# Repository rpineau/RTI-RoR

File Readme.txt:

This plugin allows you to control a dome rotation and shutter with the NexDome Dome Rotation Kit (http://www.nexdome.com/#!product-page/gba22/79b04628-9935-5ea7-9c5b-6936abac9900 ) from NexDome (shutter control should be available soon too).
This was developed and tested using a "desk" dome (see picture on my website).

The NexDome Rotation Kit firmware can be found on Gerry Rozema's GitHub : https://github.com/grozzie2/NexDome

Pre-compiled versions for OS X, Windows, Unbuntu X86_64 and Rapsberry Pi Pixel can be found there :
http://www.rti-zone.org/macosx_x2dome_plugins.php

Rodolphe

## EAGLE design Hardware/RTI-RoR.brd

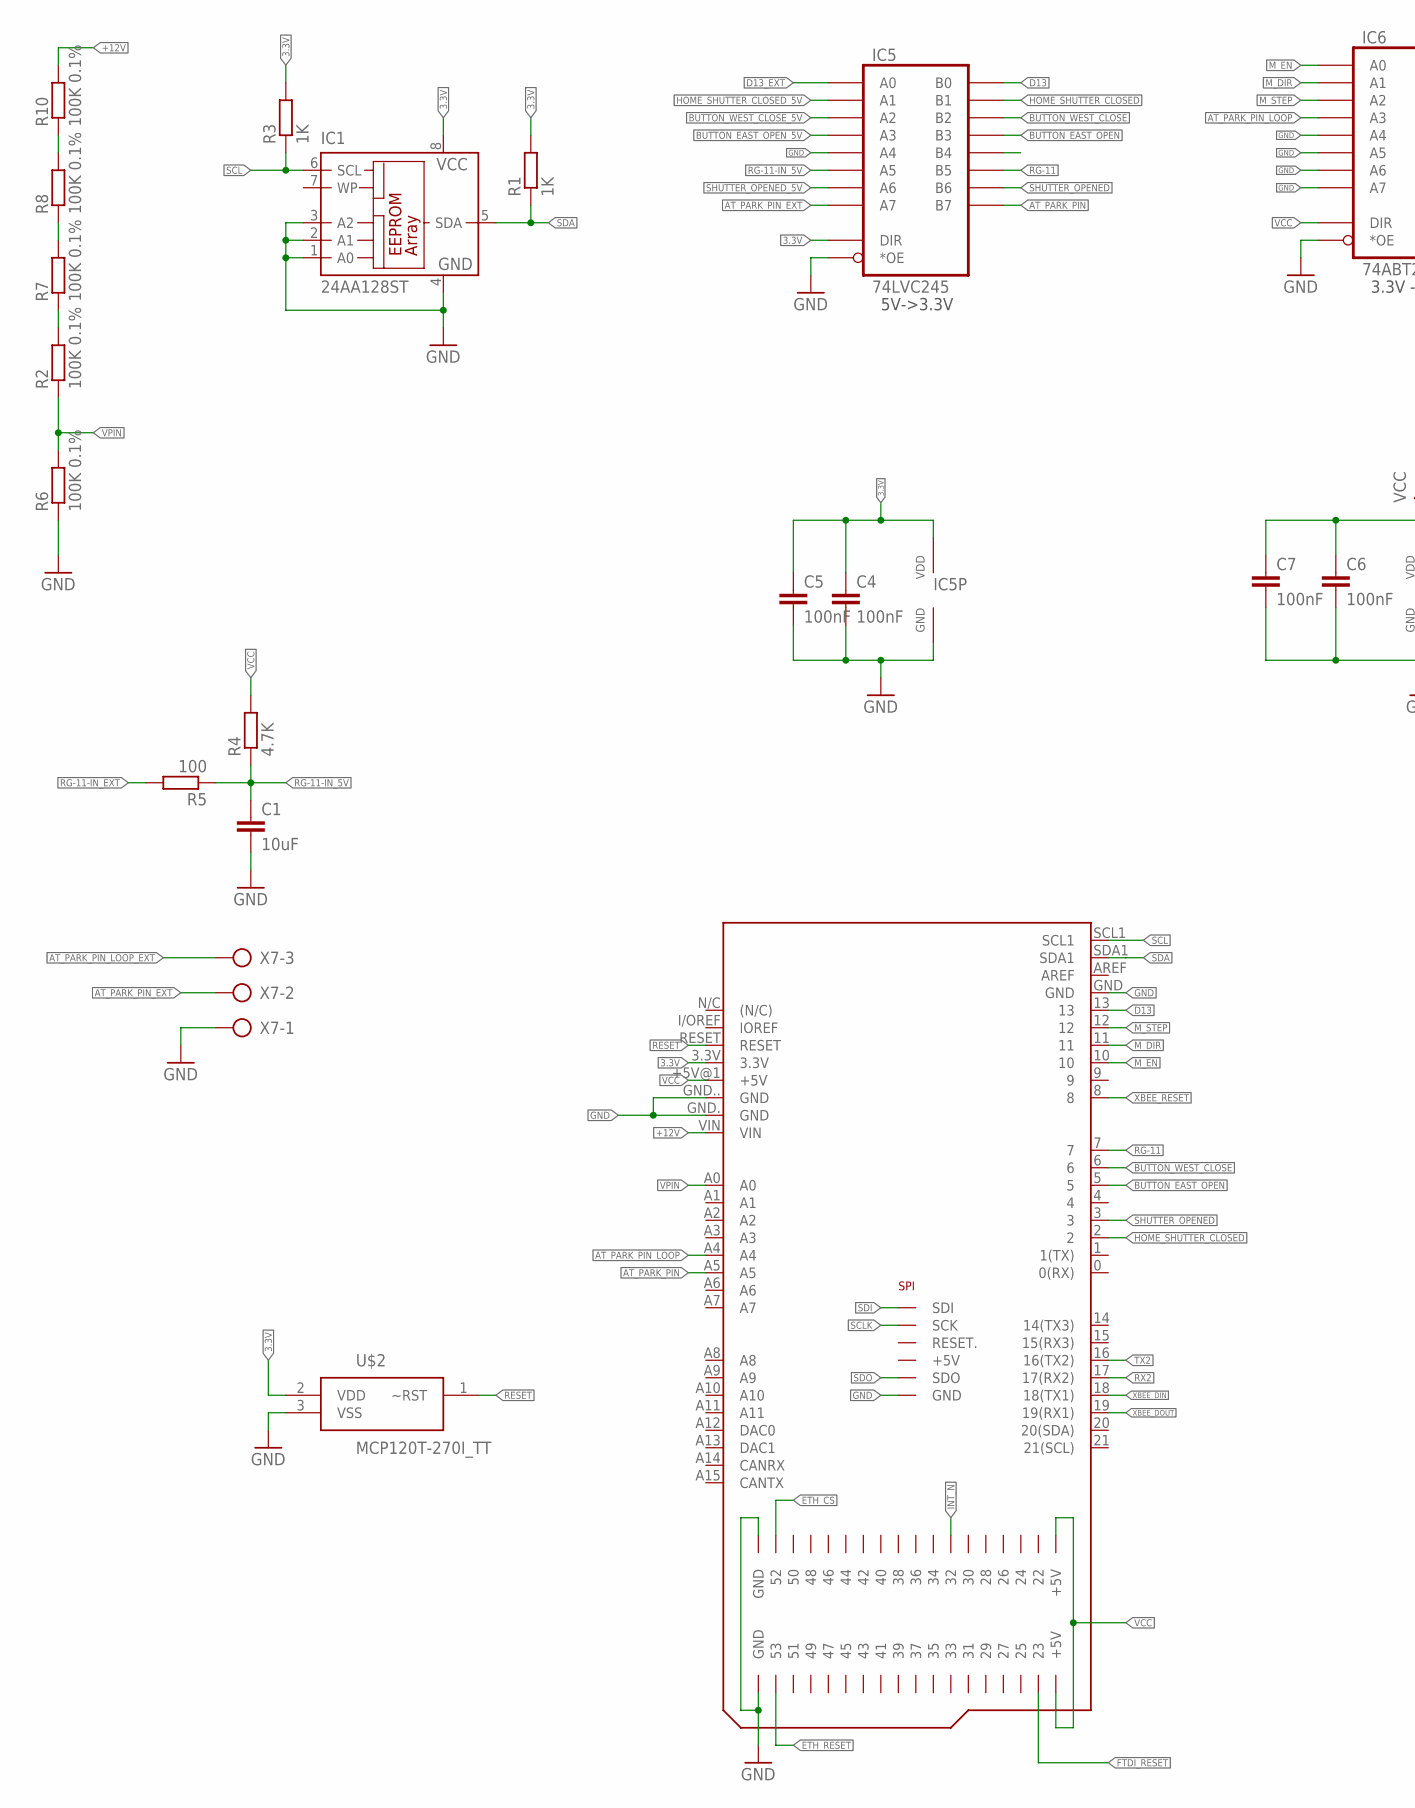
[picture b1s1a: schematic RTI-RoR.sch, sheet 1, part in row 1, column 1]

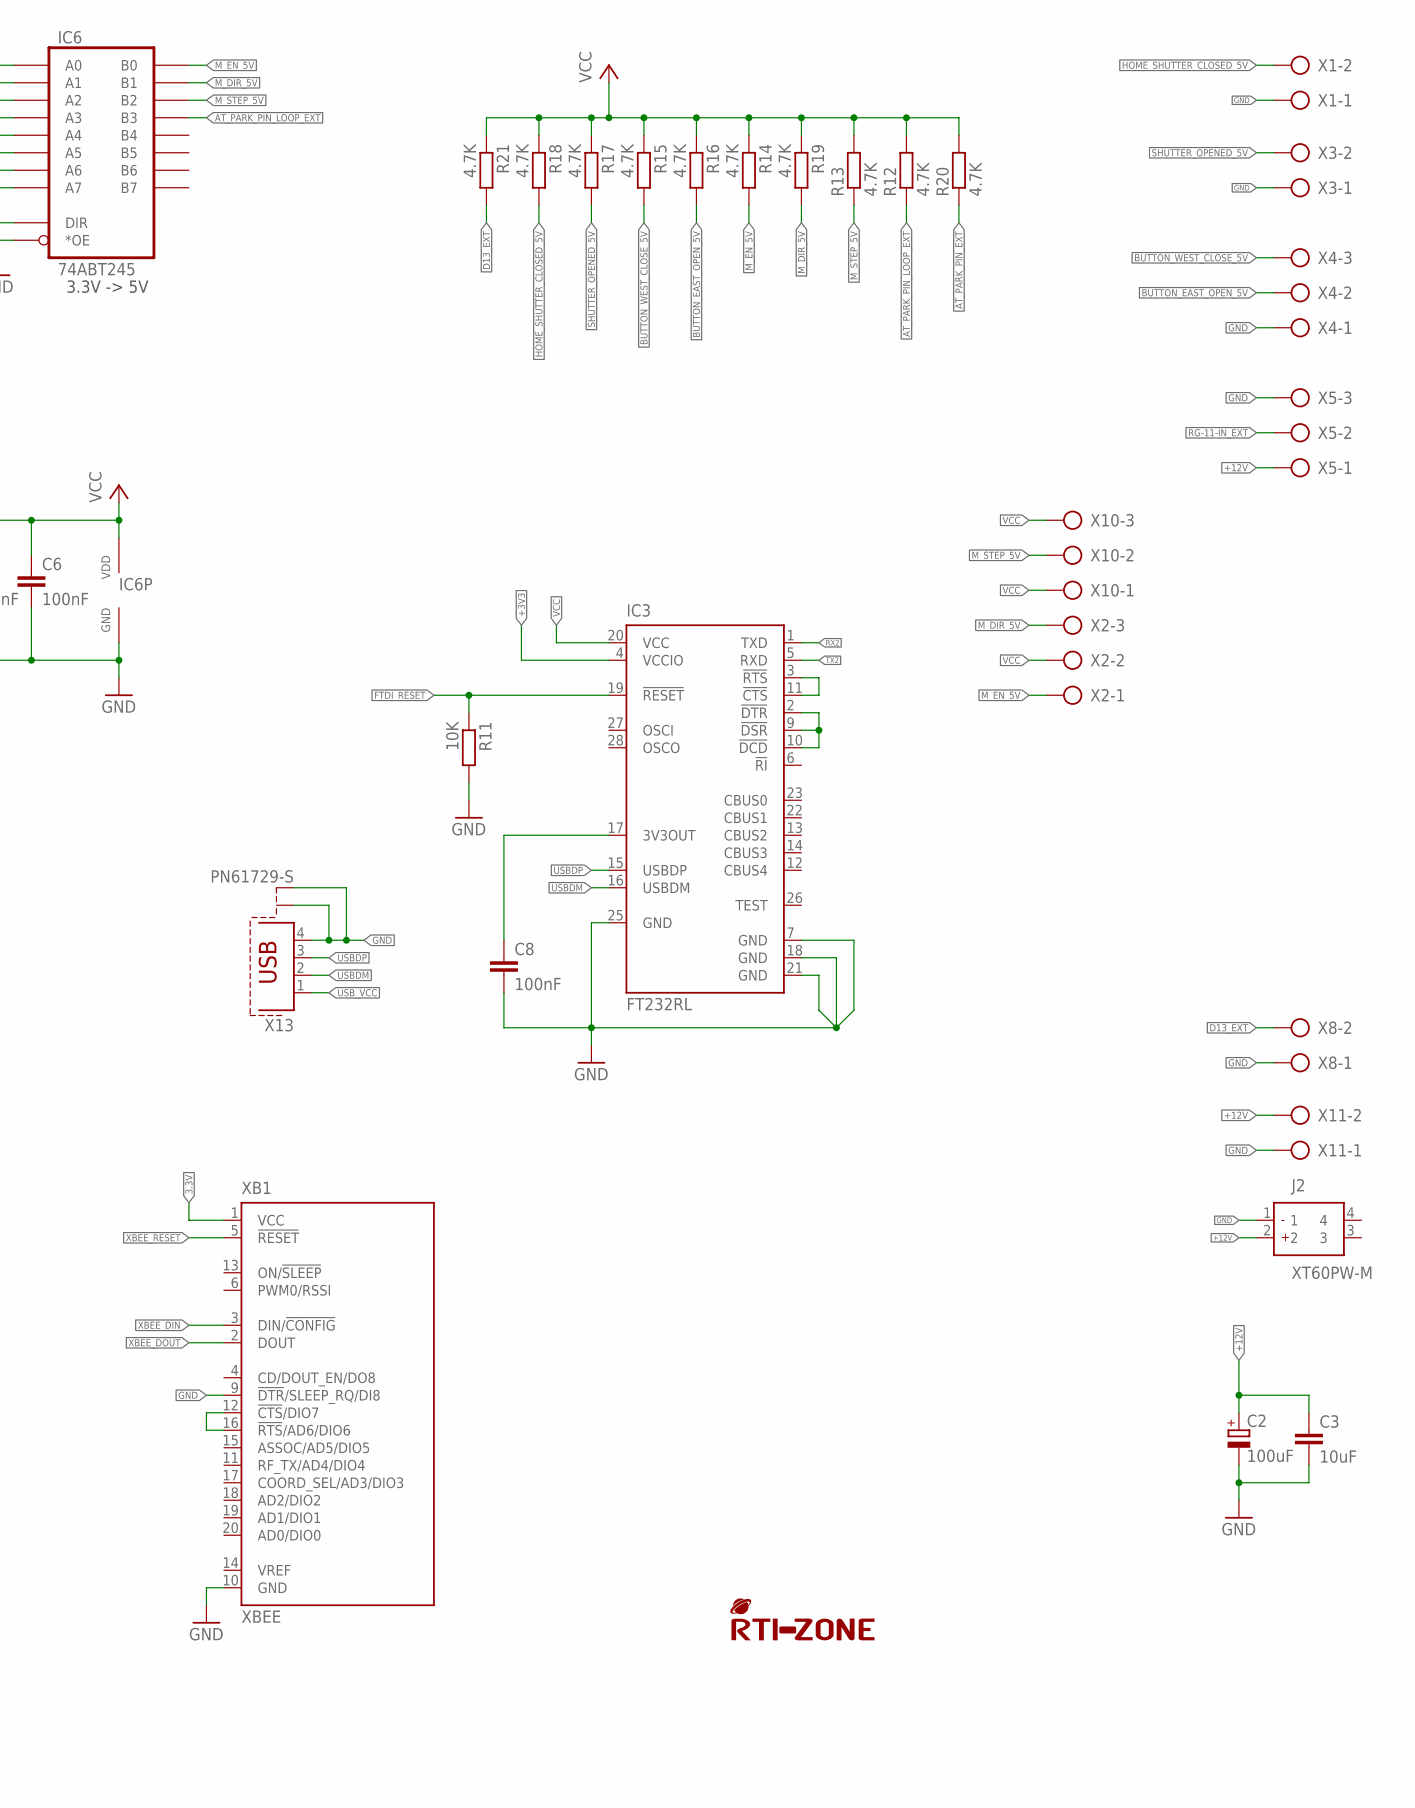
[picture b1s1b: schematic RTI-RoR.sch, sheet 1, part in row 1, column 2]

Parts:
C1, C3: 10uF; C0805; MPN CC0805KKX5R8BB106
C2: 100uF; UD-10X10_NICHICON; MPN MAL215099804E3
C4, C5, C6, C7, C8: 100nF; C0805; MPN 0805YD104KAT2A
IC1: 24AA128ST; TSSOP8
IC3: FT232RL; SSOP28; MPN FT232RL-REEL
IC5: 74LVC245; TSSOP20; MPN 74LVC245APW,112
IC6: 74ABT245; TSSOP20; MPN 74ABT245PW,112
J2: XT60PW-M; XT60PWM
R1, R3: 1K; R0805; MPN RT0805FRE071KL
R2, R6, R7, R8, R10: 100K 0.1%; R0805; MPN AT0805BRD07100KL
R4, R12, R13, R14, R15, R16, R17, R18, R19, R20, R21: 4.7K; R0805; MPN RT0805FRE074K7L
R5: 100; R0805; MPN RT0805FRD07100RL
R11: 10K; R0805; MPN RT0805FRE0710KL
U$1: ARDUINO_DUE_SHIELD_FULL
U$2: MCP120T-270I_TT; SOT95P237X112-3N; MPN MCP120T-270I/TT
U$4: RTI-LOGO_BIG; LOGO_BIG
X1, X3, X8, X11: AK500/2; MPN 691101710002
X2, X10: AK500/3
X4, X5, X7: AK500/3; MPN 691101710003
X13: PN61729-S; MPN SS-52300-001
XB1: XBEE

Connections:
3.3V: C4.1, C5.1, IC1.8 (VCC), IC5.P$1 (DIR), IC5.P$20 (VDD), R1.2, R3.2, U$1.3.3V, U$2.2 (VDD), XB1.1 (VCC)
+3V3: IC3.4 (VCCIO); also elsewhere on the board
+5V: U$1.+5V@2 (+5V)
+12V: C2.+, C3.1, J2.2, R10.2, U$1.VIN, X5.1, X11.2; also elsewhere on the board
AT_PARK_PIN: IC5.P$11 (B7), U$1.A5
AT_PARK_PIN_EXT: IC5.P$9 (A7), R20.1, X7.2
AT_PARK_PIN_LOOP: IC6.P$5 (A3), U$1.A4
AT_PARK_PIN_LOOP_EXT: IC6.P$15 (B3), R12.1, X7.3
BUTTON_EAST_OPEN: IC5.P$15 (B3), U$1.5
BUTTON_EAST_OPEN_5V: IC5.P$5 (A3), R16.2, X4.2
BUTTON_WEST_CLOSE: IC5.P$16 (B2), U$1.6
BUTTON_WEST_CLOSE_5V: IC5.P$4 (A2), R15.2, X4.3
D13: IC5.P$18 (B0), U$1.13
D13_EXT: IC5.P$2 (A0), R21.2, X8.2
DTR_DSR_DCD: IC3.2 (!DTR), IC3.9 (!DSR), IC3.10 (!DCD)
ETH_CS: U$1.52; also elsewhere on the board
ETH_RESET: U$1.53; also elsewhere on the board
FTDI_RESET: IC3.19 (!RESET), R11.1, U$1.23
GND: C1.2, C2.-, C3.2, C4.2, C5.2, C6.2, C7.2, C8.2, IC1.1 (A0), IC1.2 (A1), IC1.3 (A2), IC1.4 (GND), IC3.7 (GND), IC3.18 (GND), IC3.21 (GND), IC3.25 (GND), IC5.P$6 (A4), IC5.P$10 (GND), IC5.P$19 (*OE), IC6.P$6 (A4), IC6.P$7 (A5), IC6.P$8 (A6), IC6.P$9 (A7), IC6.P$10 (GND), IC6.P$19 (*OE), J2.1, R6.1, R11.2, U$1.GND, U$1.GND. (GND), U$1.GND.. (GND), U$1.GND... (GND), U$1.GND.... (GND), U$1.GND__ (GND), U$2.3 (VSS), X1.1, X3.1, X4.1, X5.3, X7.1, X8.1, X11.1, X13.4, X13.S1, X13.S2, XB1.9 (!DTR!/SLEEP_RQ/DI8), XB1.10 (GND); also elsewhere on the board
HOME_SHUTTER_CLOSED: IC5.P$17 (B1), U$1.2
HOME_SHUTTER_CLOSED_5V: IC5.P$3 (A1), R18.2, X1.2
INT_N: U$1.32; also elsewhere on the board
M_DIR: IC6.P$3 (A1), U$1.11
M_DIR_5V: IC6.P$17 (B1), R19.2, X2.3
M_EN: IC6.P$2 (A0), U$1.10
M_EN_5V: IC6.P$18 (B0), R14.2, X2.1
M_STEP: IC6.P$4 (A2), U$1.12
M_STEP_5V: IC6.P$16 (B2), R13.1, X10.2
unnamed: R7.2, R8.1
unnamed: R8.2, R10.1
unnamed: R2.2, R7.1
unnamed: C8.1, IC3.17 (3V3OUT)
unnamed: XB1.12 (!CTS!/DIO7), XB1.16 (!RTS!/AD6/DIO6)
RESET: U$1.RESET, U$2.1 (~RST)
RG-11: IC5.P$13 (B5), U$1.7
RG-11-IN_5V: C1.1, IC5.P$7 (A5), R4.1, R5.1
RG-11-IN_EXT: R5.2, X5.2
RTS_CTS: IC3.3 (!RTS), IC3.11 (!CTS)
RX2: IC3.1 (TXD), U$1.17 (17(RX2))
SCL: IC1.6 (SCL), R3.1, U$1.SCL1
SCLK: U$1.SCK; also elsewhere on the board
SDA: IC1.5 (SDA), R1.1, U$1.SDA1
SDI: U$1.MISO (SDI); also elsewhere on the board
SDO: U$1.MOSI (SDO); also elsewhere on the board
SHUTTER_OPENED: IC5.P$12 (B6), U$1.3
SHUTTER_OPENED_5V: IC5.P$8 (A6), R17.2, X3.2
TX2: IC3.5 (RXD), U$1.16 (16(TX2))
USBDM: IC3.16 (USBDM), X13.2
USBDP: IC3.15 (USBDP), X13.3
USB_VCC: X13.1
VCC: C6.1, C7.1, IC3.20 (VCC), IC6.P$1 (DIR), IC6.P$20 (VDD), R4.2, R12.2, R13.2, R14.1, R15.1, R16.1, R17.1, R18.1, R19.1, R20.2, R21.1, U$1.+5V@1 (+5V), U$1.+5V@3 (+5V), U$1.+5V@4 (+5V), X2.2, X10.1, X10.3
VPIN: R2.1, R6.2, U$1.A0
XBEE_DIN: U$1.18 (18(TX1)), XB1.3 (DIN/!CONFIG)
XBEE_DOUT: U$1.19 (19(RX1)), XB1.2 (DOUT)
XBEE_RESET: U$1.8, XB1.5 (!RESET)

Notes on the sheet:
5V->3.3V
3.3V -> 5V

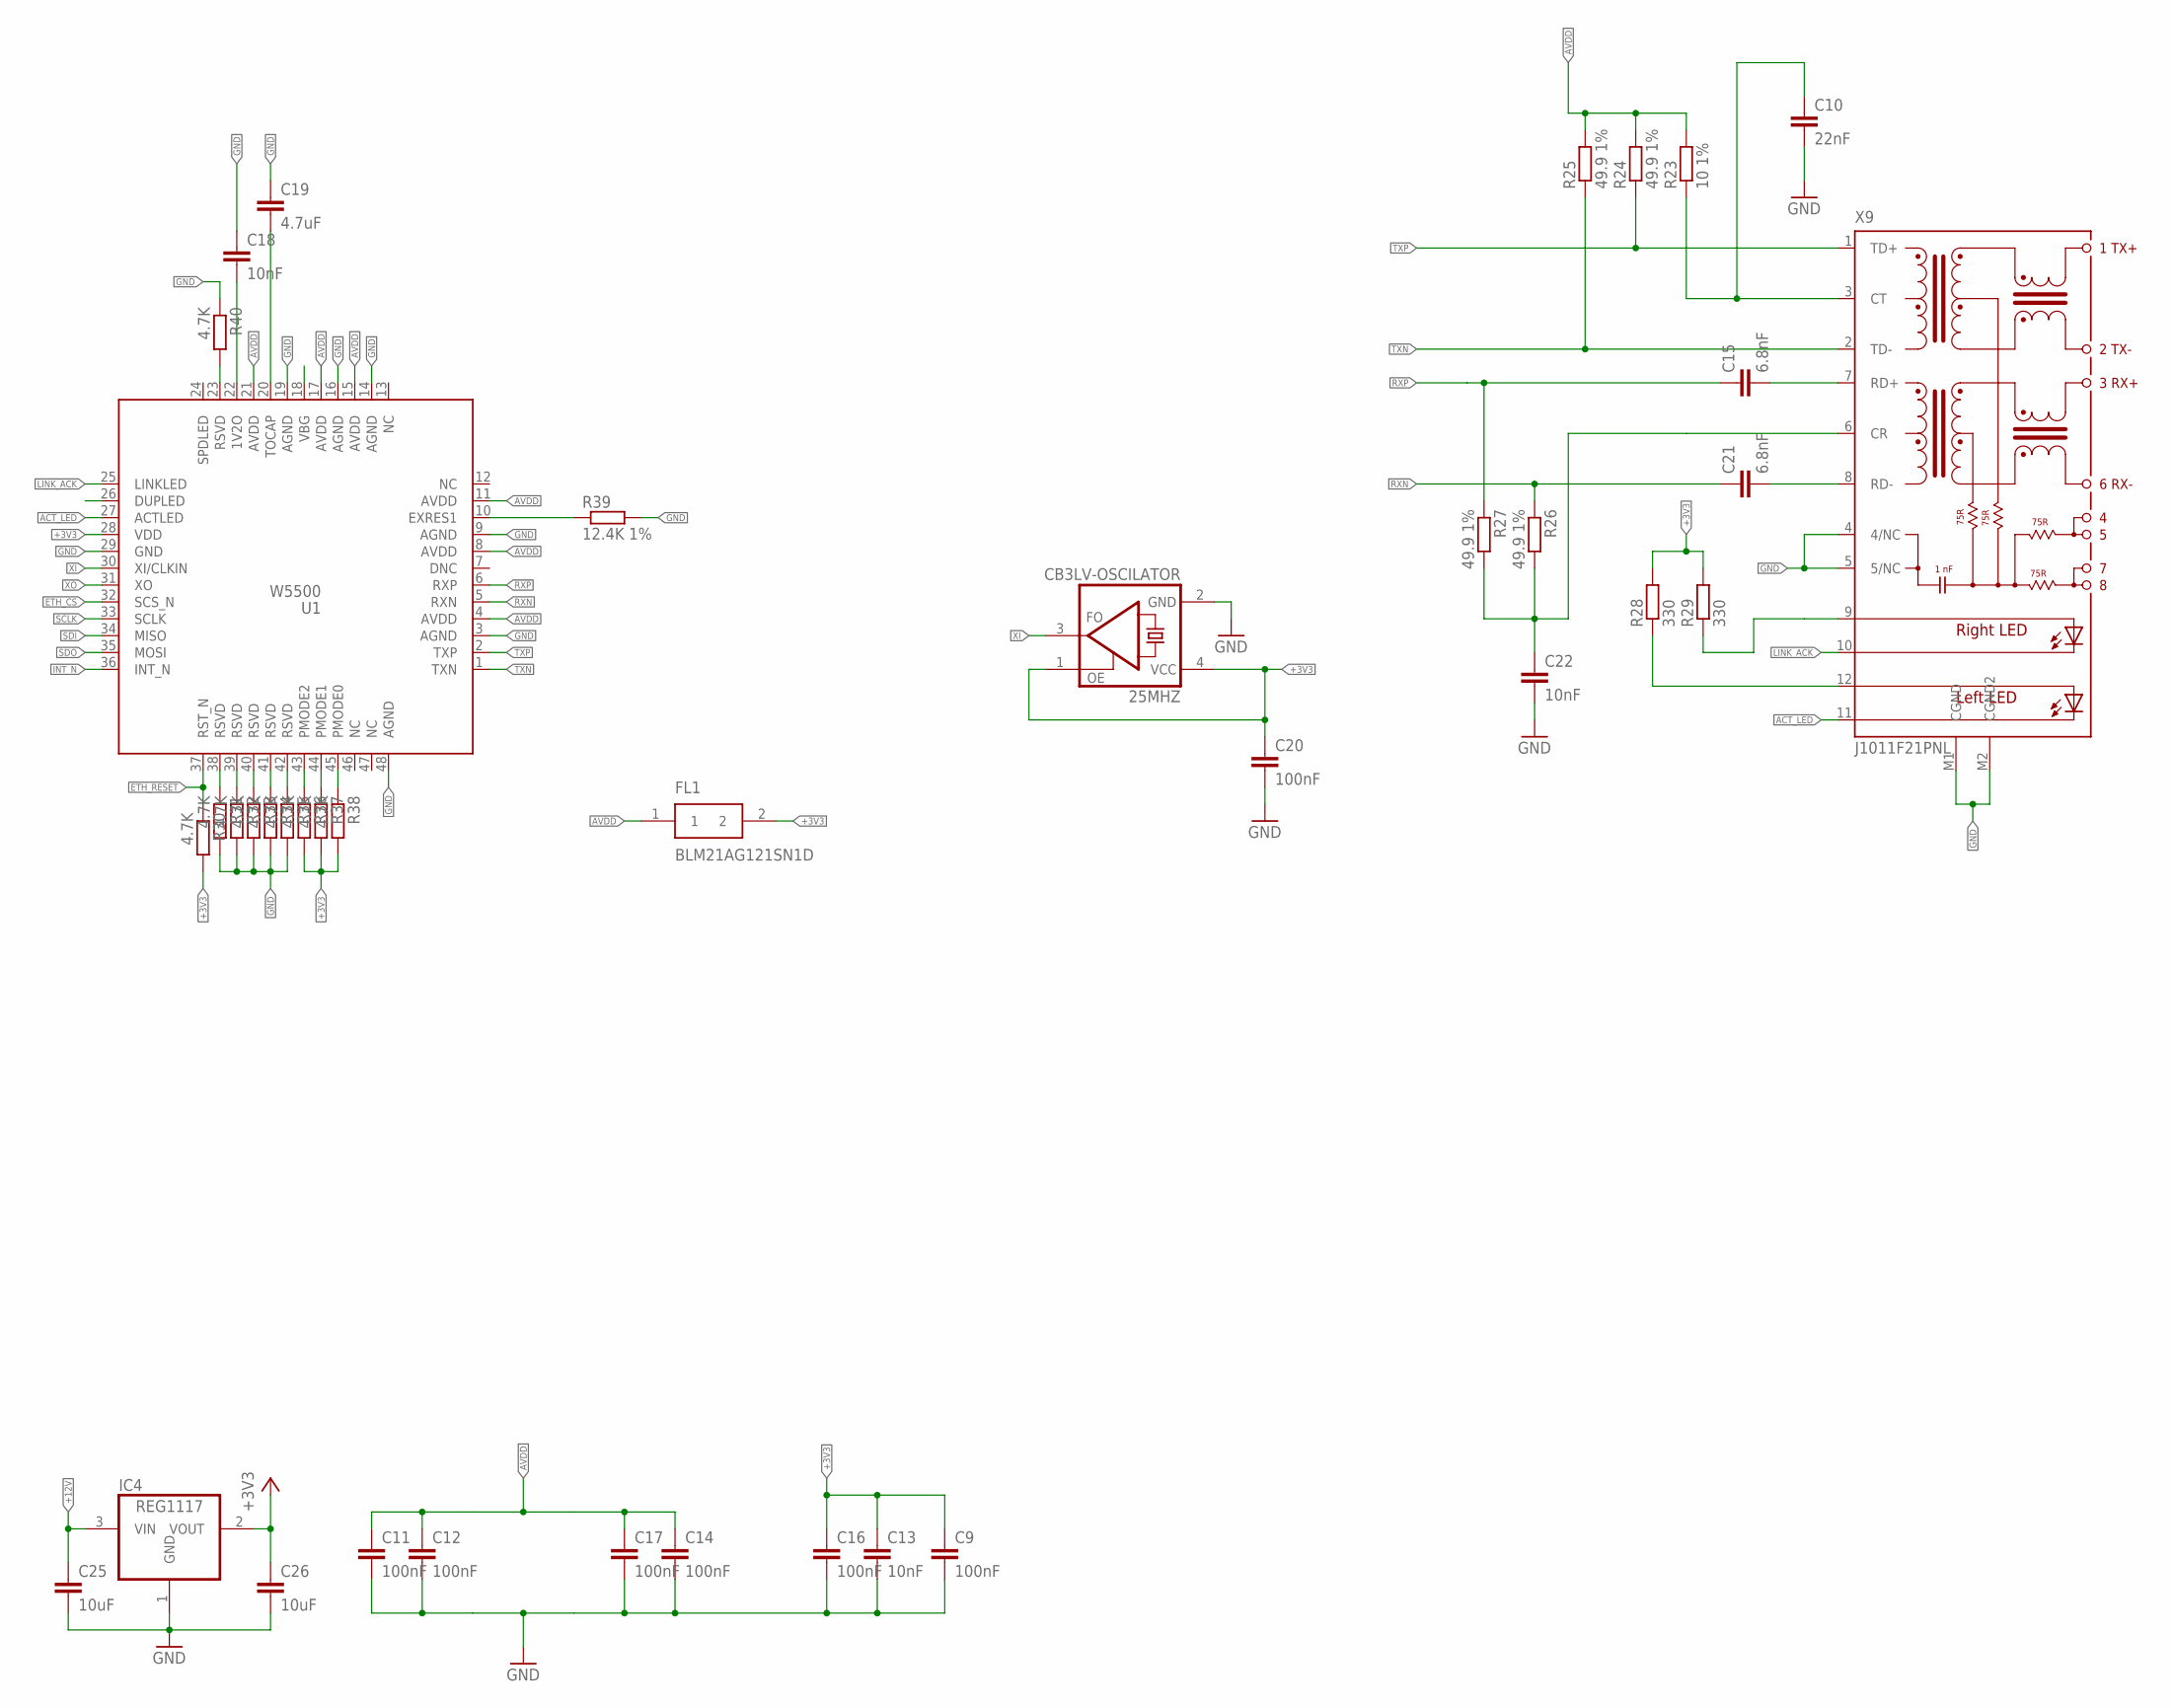
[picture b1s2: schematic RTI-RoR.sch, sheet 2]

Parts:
25MHZ: CB3LV-OSCILATOR; SMD-7050_4P; MPN CB3LV-3I-25M0000
C9, C11, C12, C14, C16, C17, C20: 100nF; C0805; MPN 0805YD104KAT2A
C10: 22nF; C0805; MPN CC0805JRX7R8BB223
C13, C18, C22: 10nF; C0805; MPN CC0805KRX7R9BB103
C15, C21: 6.8nF; C0805; MPN C0805C682F4HACTU
C19: 4.7uF; C0805; MPN C0805C475J3RACTU
C25, C26: 10uF; C0805; MPN CC0805KKX5R8BB106
FL1: BLM21AG121SN1D; L0805; MPN BLM21AG121SN1D
IC4: REG1117; SOT223; MPN REG1117-3.3/2K5
R23: 10 1%; R0805; MPN RT0805FRE1310RL
R24, R25, R26, R27: 49.9 1%; R0805; MPN RC0805FR-0749R9L
R28, R29: 330; R0805; MPN RC0805JR-07330RL
R30, R31, R32, R33, R34, R35, R36, R37, R38, R40: 4.7K; R0805; MPN RT0805FRE074K7L
R39: 12.4K 1%; R0805; MPN RC0805FR-0712K4L
U1: W5500; LQFP48; MPN W5500
X9: J1011F21PNL; MPN J1011F21PNL

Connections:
+3V3: 25MHZ.1 (OE), 25MHZ.4 (VDD), C9.1, C13.1, C16.1, C20.1, C26.1, FL1.2, IC4.2 (VOUT), R28.2, R29.2, R30.2, R36.2, R37.2, R38.2, U1.28 (VDD); also elsewhere on the board
+12V: C25.1, IC4.3 (VIN); also elsewhere on the board
ACT_LED: U1.27 (ACTLED), X9.11 (C-L)
AVDD: C11.1, C12.1, C14.1, C17.1, FL1.1, R23.2, R24.2, R25.2, U1.4 (AVDD), U1.8 (AVDD), U1.11 (AVDD), U1.15 (AVDD), U1.17 (AVDD), U1.21 (AVDD)
ETH_CS: U1.32 (SCS_N); also elsewhere on the board
ETH_RESET: R30.1, U1.37 (RST_N); also elsewhere on the board
GND: 25MHZ.2 (GND), C9.2, C10.2, C11.2, C12.2, C13.2, C14.2, C16.2, C17.2, C18.1, C19.1, C20.2, C22.2, C25.2, C26.2, IC4.1 (GND), R31.2, R32.2, R33.2, R34.2, R35.2, R39.2, R40.1, U1.3 (AGND), U1.9 (AGND), U1.14 (AGND), U1.16 (AGND), U1.19 (AGND), U1.29 (GND), U1.48 (AGND), X9.4 (4/NC), X9.5 (5/NC), X9.M1 (CGND), X9.M2 (CGND2); also elsewhere on the board
INT_N: U1.36 (INT_N); also elsewhere on the board
LINK_ACK: U1.25 (LINKLED), X9.10 (C-R)
unnamed: C22.1, R26.2, R27.2, X9.6 (CR)
unnamed: R29.1, X9.9 (A-R)
unnamed: R28.1, X9.12 (AL)
unnamed: C15.2, X9.7 (RD+)
unnamed: C21.2, X9.8 (RD-)
unnamed: C10.1, R23.1, X9.3 (CT)
unnamed: R31.1, U1.38 (RSVD)
unnamed: R32.1, U1.39 (RSVD)
unnamed: R33.1, U1.40 (RSVD)
unnamed: R34.1, U1.41 (RSVD)
unnamed: R35.1, U1.42 (RSVD)
unnamed: R36.1, U1.43 (PMODE2)
unnamed: R37.1, U1.44 (PMODE1)
unnamed: R38.1, U1.45 (PMODE0)
unnamed: C19.2, U1.20 (TOCAP)
unnamed: C18.2, U1.22 (1V2O)
unnamed: R39.1, U1.10 (EXRES1)
unnamed: R40.2, U1.23 (RSVD)
RXN: C21.1, R26.1, U1.5 (RXN)
RXP: C15.1, R27.1, U1.6 (RXP)
SCLK: U1.33 (SCLK); also elsewhere on the board
SDI: U1.34 (MISO); also elsewhere on the board
SDO: U1.35 (MOSI); also elsewhere on the board
TXN: R25.1, U1.1 (TXN), X9.2 (TD-)
TXP: R24.1, U1.2 (TXP), X9.1 (TD+)
XI: 25MHZ.3 (FO), U1.30 (XI/CLKIN)
XO: U1.31 (XO)

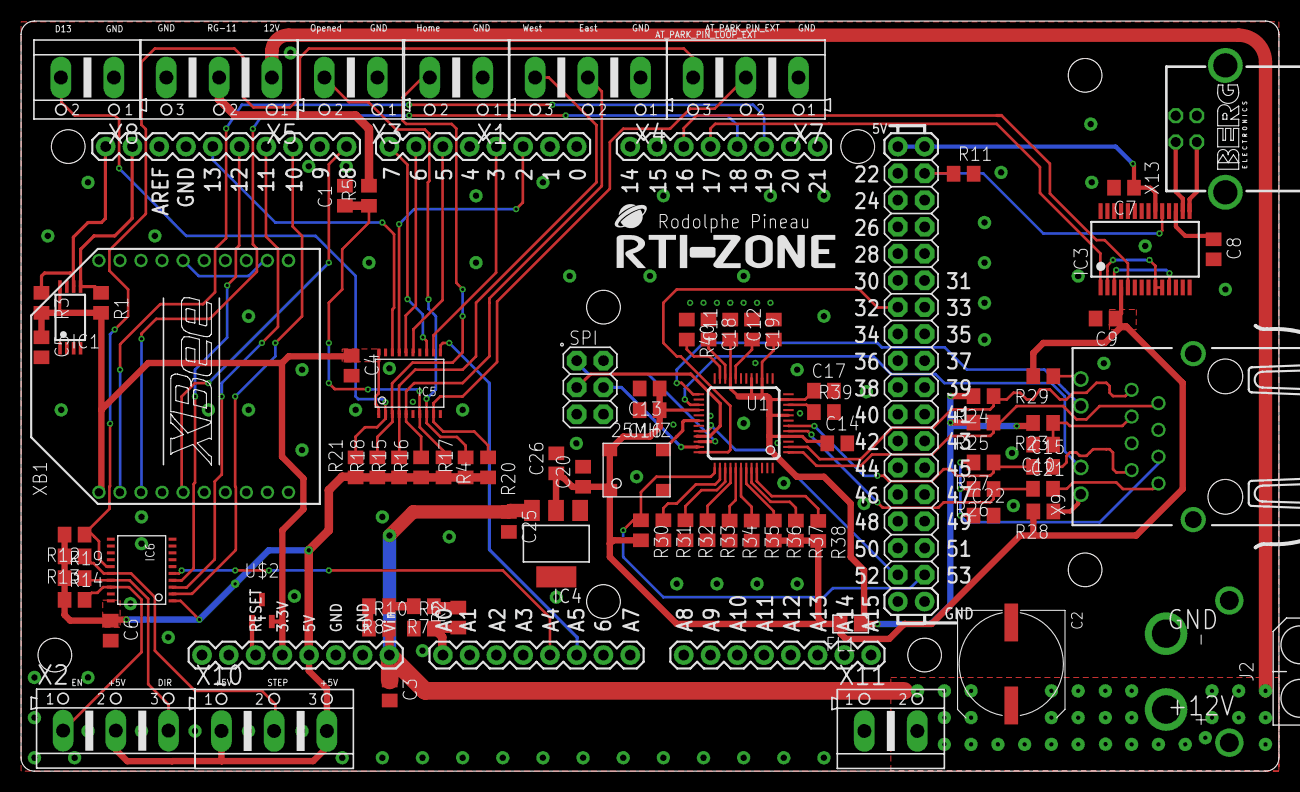
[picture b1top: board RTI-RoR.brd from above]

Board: 2 copper layers, 119.4 x 71.2 mm, 86 parts (0 on the bottom side), 79 nets.

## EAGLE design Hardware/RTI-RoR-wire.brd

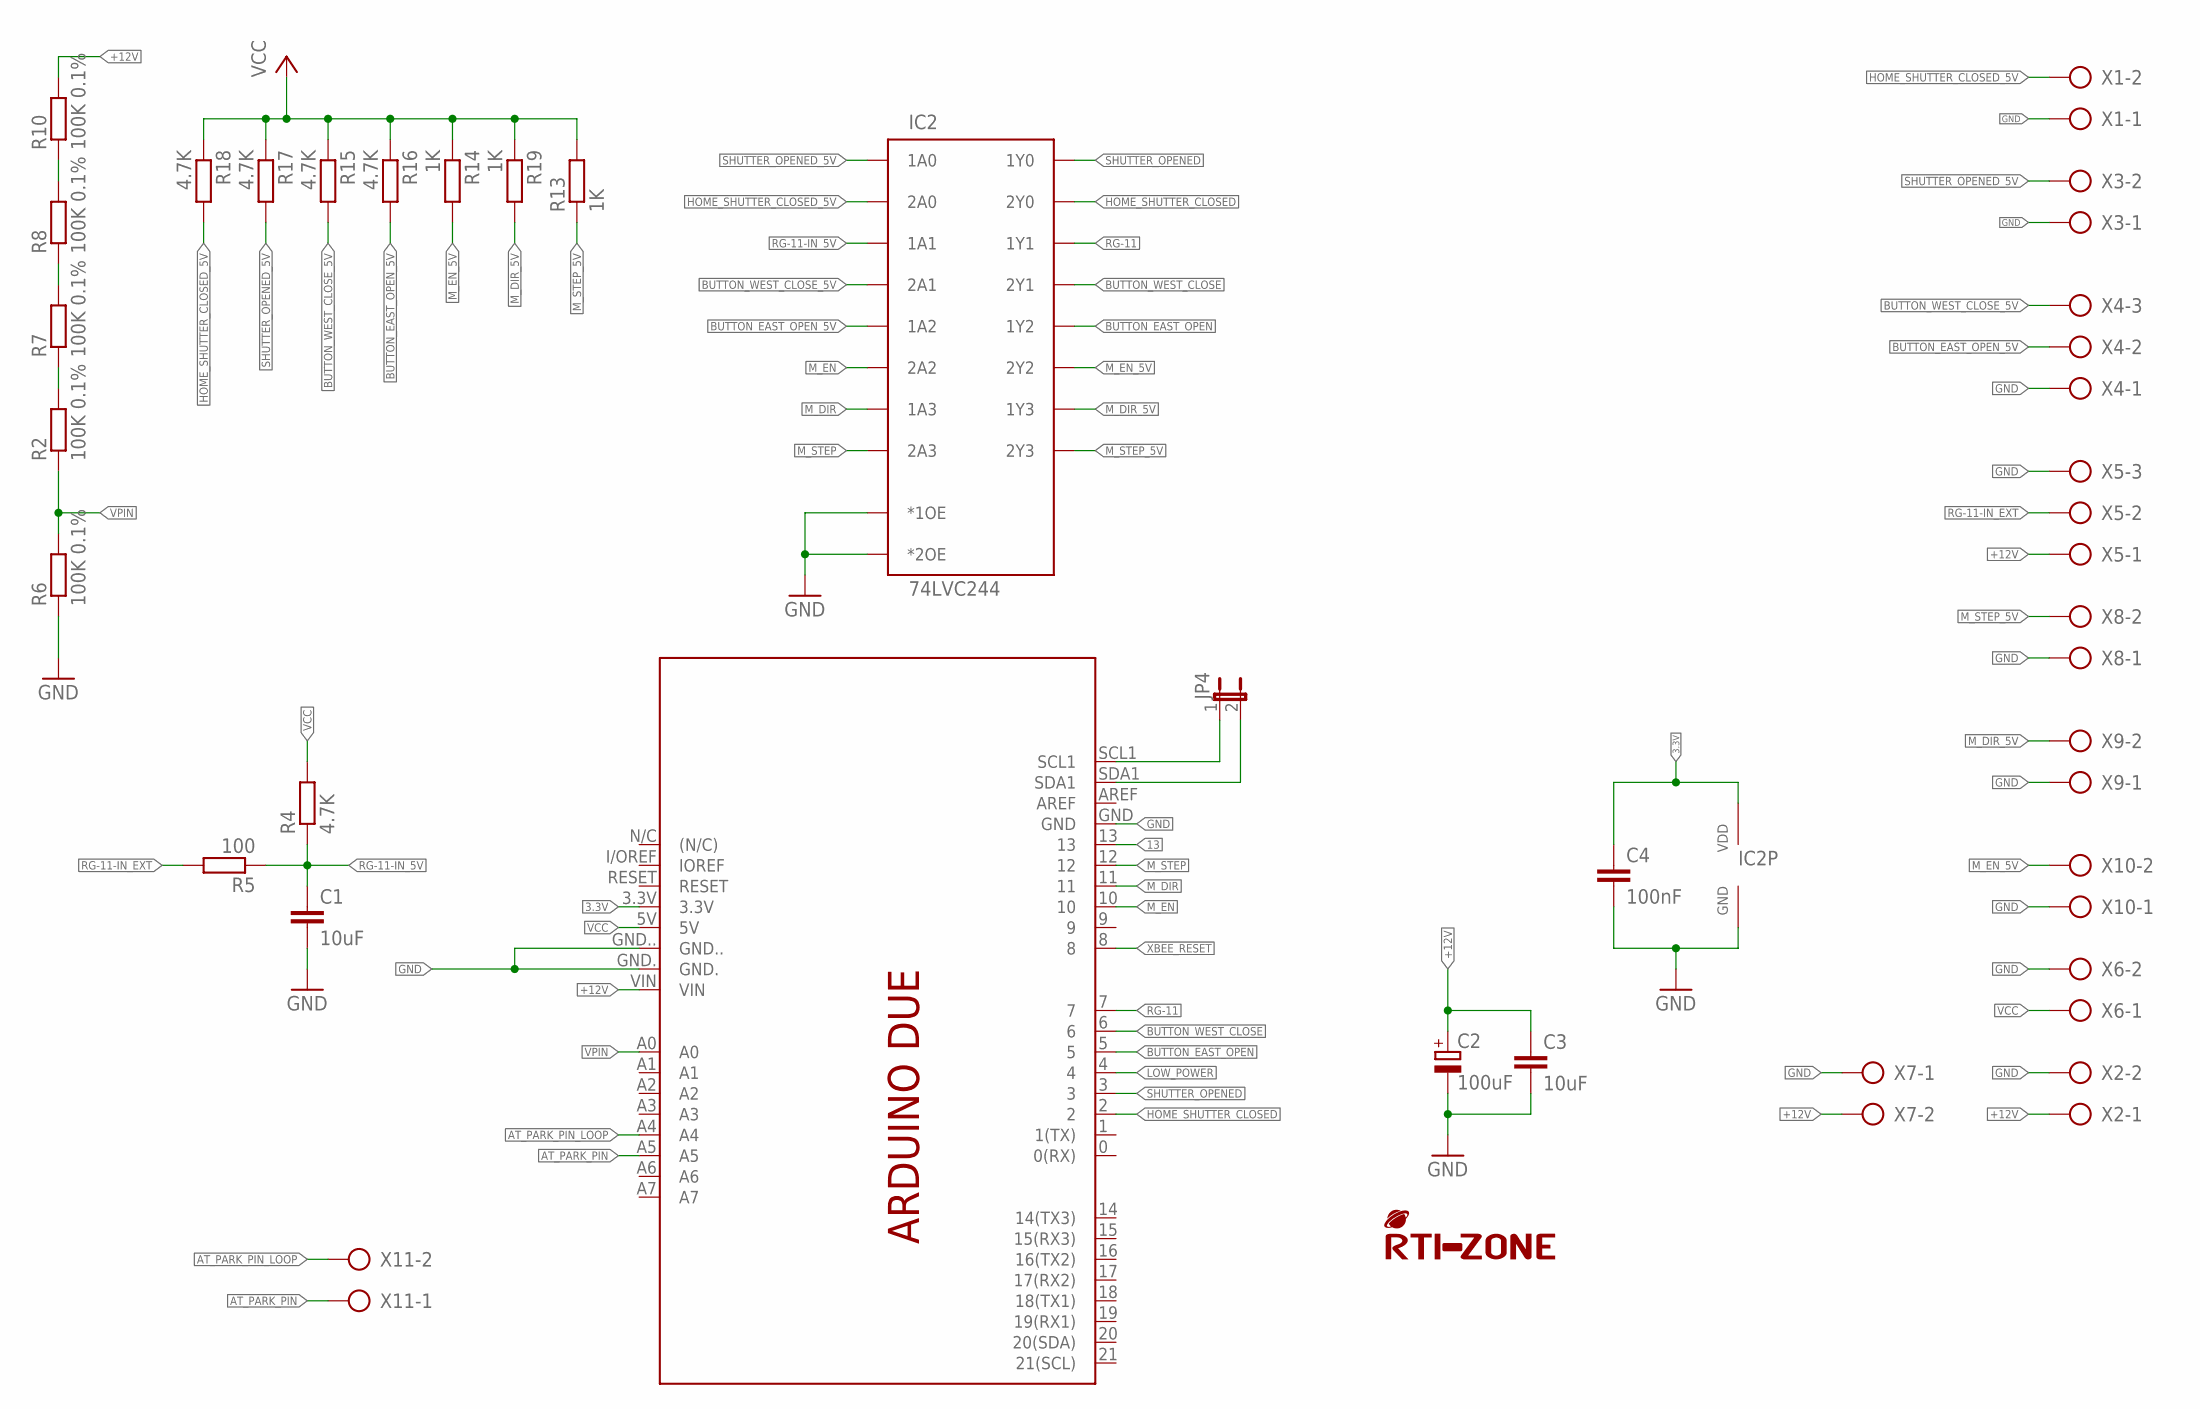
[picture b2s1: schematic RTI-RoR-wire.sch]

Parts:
C1, C3: 10uF; C0805
C2: 100uF; UD-10X10_NICHICON
C4: 100nF; C0805
IC2: 74LVC244; TSSOP20
JP4: JP1E; JP1
PCB1: ARDUINO_DUE_SHIELD_SHORT
R2, R6, R7, R8, R10: 100K 0.1%; R0805
R4, R15, R16, R17, R18: 4.7K; R0805
R5: 100; R0805
R13, R14, R19: 1K; R0805
U$4: RTI-LOGO_BIG; LOGO_BIG
X1, X2, X3, X6, X7, X8, X9, X10, X11: AK500/2
X4, X5: AK500/3

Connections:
3.3V: C4.1, IC2.P$20 (VDD), PCB1.3.3V
13: PCB1.13
+12V: C2.+, C3.1, PCB1.VIN, R10.2, X2.1, X5.1, X7.2
AT_PARK_PIN: PCB1.A5, X11.1
AT_PARK_PIN_LOOP: PCB1.A4, X11.2
BUTTON_EAST_OPEN: IC2.P$14 (1Y2), PCB1.5
BUTTON_EAST_OPEN_5V: IC2.P$6 (1A2), R16.2, X4.2
BUTTON_WEST_CLOSE: IC2.P$5 (2Y1), PCB1.6
BUTTON_WEST_CLOSE_5V: IC2.P$15 (2A1), R15.2, X4.3
GND: C1.2, C2.-, C3.2, C4.2, IC2.P$1 (*1OE), IC2.P$10 (GND), IC2.P$19 (*2OE), PCB1.GND, PCB1.GND., PCB1.GND.., R6.1, X1.1, X2.2, X3.1, X4.1, X5.3, X6.2, X7.1, X8.1, X9.1, X10.1
HOME_SHUTTER_CLOSED: IC2.P$3 (2Y0), PCB1.2
HOME_SHUTTER_CLOSED_5V: IC2.P$17 (2A0), R18.2, X1.2
LOW_POWER: PCB1.4
M_DIR: IC2.P$8 (1A3), PCB1.11
M_DIR_5V: IC2.P$12 (1Y3), R19.2, X9.2
M_EN: IC2.P$13 (2A2), PCB1.10
M_EN_5V: IC2.P$7 (2Y2), R14.2, X10.2
M_STEP: IC2.P$11 (2A3), PCB1.12
M_STEP_5V: IC2.P$9 (2Y3), R13.1, X8.2
unnamed: R7.2, R8.1
unnamed: R8.2, R10.1
unnamed: R2.2, R7.1
unnamed: JP4.1, PCB1.SCL1
unnamed: JP4.2, PCB1.SDA1
RG-11: IC2.P$16 (1Y1), PCB1.7
RG-11-IN_5V: C1.1, IC2.P$4 (1A1), R4.1, R5.1
RG-11-IN_EXT: R5.2, X5.2
SHUTTER_OPENED: IC2.P$18 (1Y0), PCB1.3
SHUTTER_OPENED_5V: IC2.P$2 (1A0), R17.2, X3.2
VCC: PCB1.5V, R4.2, R13.2, R14.1, R15.1, R16.1, R17.1, R18.1, R19.1, X6.1
VPIN: PCB1.A0, R2.1, R6.2
XBEE_RESET: PCB1.8

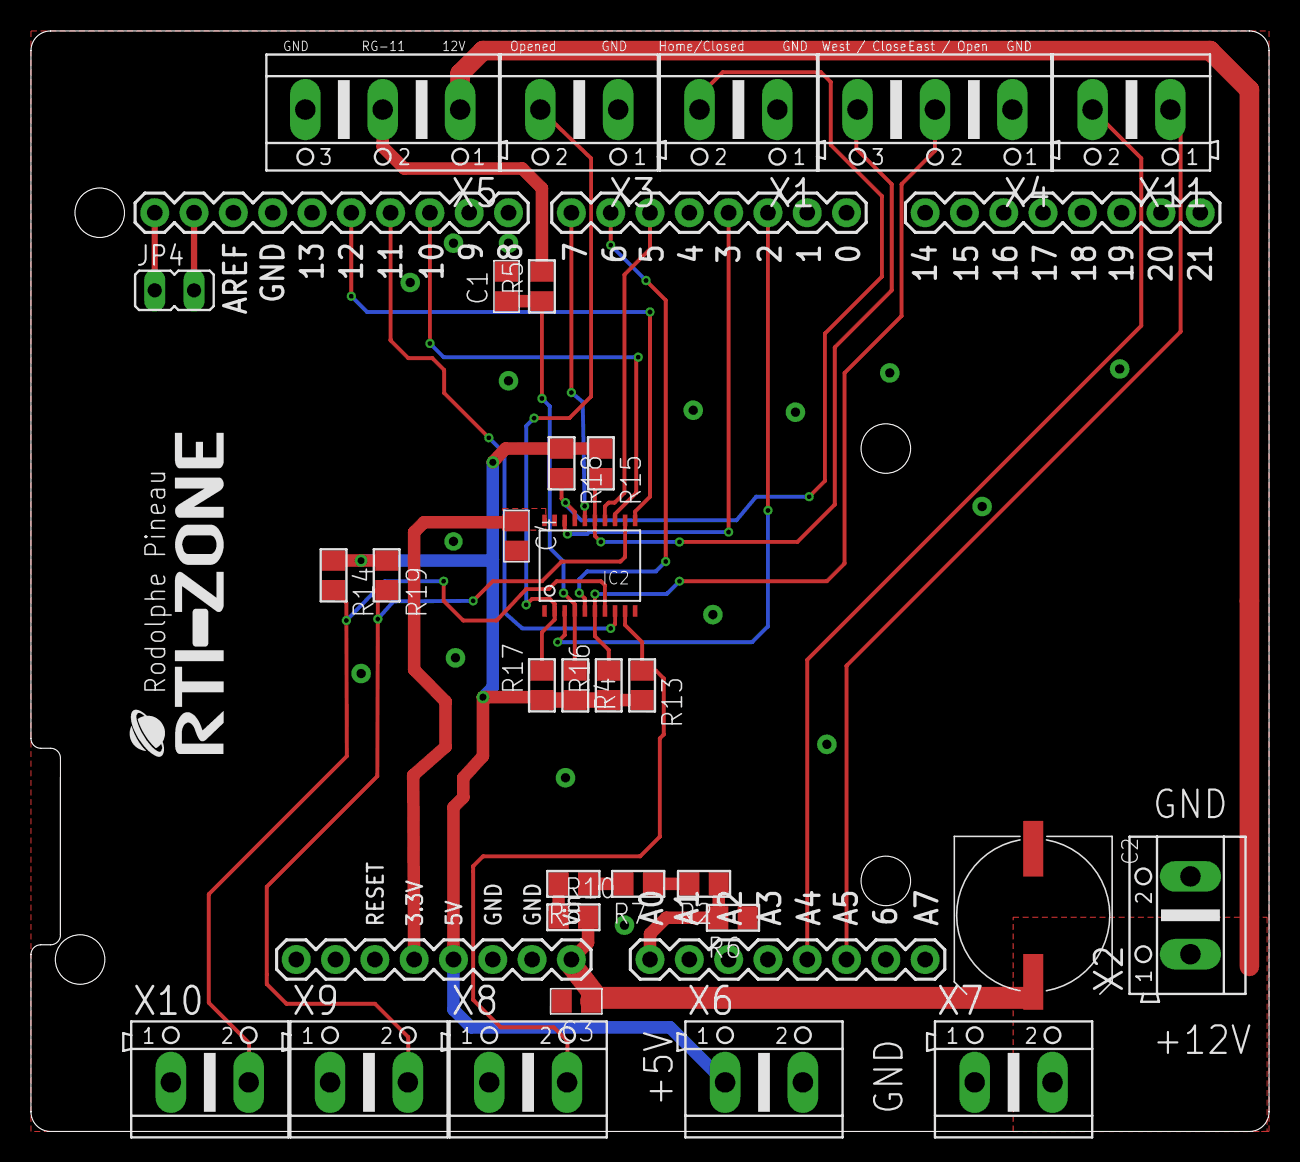
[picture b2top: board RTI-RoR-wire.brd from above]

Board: 2 copper layers, 80.0 x 71.1 mm, 33 parts (0 on the bottom side), 29 nets.

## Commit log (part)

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2019-07-09 initial import
2019-07-19 fix arm64 install path
2019-11-11 Fix project and plugin name
2020-01-03 Add notarization and new install
2020-01-05 fix install path for macOS 64bit notarized bundle
2020-01-06 fix script error
2020-03-19 fix postinstall on all projects
2020-10-07 Changing connection speed for the Arduino DUE. Changing RTO Logo
2020-10-08 Fix domelist file
2020-10-08 Adding firmware here.
2020-10-09 Adding hardware and finrmware files
2020-10-12 Adding the at park pins to both PCB for the Arduino DUE.
2020-10-12 De-tab
2020-10-15 Implement interrupts for the stepper. Arduino DUE ONLY
2020-10-16 Rename directory
2020-11-09 Use the same board as the dome.
2020-11-13 fix for Xcode 12 and dual arch arn64 anbd x86_64
2021-03-21 Adding Windows 64 bits installer code
2021-06-26 fix missing windows dll static linking for 64 bits
2021-06-26 fix win 64 dll build.. part 2
2022-06-29 Update macOS notarization
2022-10-19 Re-base the code with the dome code
2023-08-08 Updating code based on RTI-Dome current one.
2023-08-19 Fix installer to copy the right image.
2023-08-21 Fix installers.
2023-08-28 ome fixes in the button managment
2023-09-05 Fixing some UI labels.
2023-10-02 Moving to RP2040
2023-10-24 Use command definitions instead of direct char in commands
2025-07-19 Started new RoR ESP32 firmware with Alpaca
2025-07-19 Fix domelist description
2025-07-29 More fix for ESP32 version
2025-08-04 More Alpaca code fix
2025-08-18 RoR esp32 firmware Ready for first test.
2025-08-19 Small fix for end of movements
2025-09-03 Put all define in a config file
2025-09-03 Fix some define in main code.
2025-09-28 Cleanup
2025-09-28 Fix RoR commands
2025-11-17 Add inverface V3 methods
2025-12-08 Adding changes made in Alpaca code on the Rotator version.
2025-12-09 Migrated config storage to ESP32 Preferences
2025-12-11 Converterd all setting to using ESP32 NVS / Preferences
2026-01-05 Switch to FastAccelStepper.
2026-05-16 Convert to FastAccelStepper, fix all preferences access
2026-05-17 Adding openapi yaml file.
2026-05-17 Started conversion to ESP32 Network stack
